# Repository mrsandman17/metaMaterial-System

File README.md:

# metaMaterial-System
The experiment system is used to measure transmission and reflection coefficents (S params) of a metamaterial.
The system includes a Keysight network Analyser to perform the measurement. A modifield CNC machine, controlled by an arduino unit, is used to move the metamaterial in order to perform measurements along an axis.
This repository details the programmtic aspect of the system. The getting started section will walk trough performing first measurements with the system. The About the System section will specify more details required to add more functinality or debug the system.

## Getting started
You can download the entire repository by clicking "Code" on the top right of the files window, and then "Download Zip".

### Measuring S parameters

#### Using the network analyser GUI
First connect your board for a S paramaters measurement. Like this:

We will test the system using the network analyser GUI by performing a measurement of S11 Parameter.
By using the program "Network Analyser" you can perform a simple measurement.
In order to perform the measurement:
1. Start the program "Network Analyser"
2. A window will pop out, select the instrument and press "Run"

3. Click "Power" -> "RF Power" -> "On"

4. You can change the number of sample points using "Sweep".

5. You can change the frequency range using "Freq"

5. Select "Trace" and press "Trace 1" to add a new trace.

6. Use "Meas" to select the S11 parameter

You now should be able to see your data. Note that clicking on "Preset" will also create a measurement of S11 parameter.
S21 parameter can be added by adding "Trace 2" in "Trace", and then selecting S21 in "Meas".

#### Measuring S parameters using the example script
After we verfied our data is good, we can automate the measurement process. A working code example is available in this repo.
The script  "measure_Sparams.m" is used to take a measurement of S11 and S21 parameters at a specified frequency range.
The script will connect to keysight network analyser, sample the data and plot S21 and S11 params. 
The frequency range can be changed with "START_FREQ" or "END_FREQ" constants.
The script does not set the number of sample points, this should be done through the GUI, as specified before, make sure to set "POINTS_NUM" constant to the same value.  

### Measuring X field
We can now measure the transmission field over an axis. For this purpose we will control an Arduino unit, the unit will control a motor which is  moving the surface the board is on.  In this measurement,  One cable is connected to the board and another functions as a sensor that scans the board. 

Connect the measure field system hardware (**Not detailed here**)

We will command the Arduino using GRBL. The current Arduino should already have the grbl library code uploaded, but if it doesn't, it can be found in this repo, under "grblUpload". It should be uploaded to the arudino unit (**Only on first use**).
This can be done via arduino gui, click on the file "grblUpload" and then upload it:

When the arduino is ready, we can communicate with it by sending GCode commands. We will first communicate with it using a java based program called "Universal-Gcode-Sender". Using the program, connect to the arduino port (Usually “COM3”) and try to send a command that will move the the motor a bit to one side (For instance, send X+ with a Step size of 0.1). 

Note that The GCODE commands you send are printed, We will later send those commands via Matlab. 

When you are done, make sure to disconnect from the arduino by clicking on close, this will free up the COM port.
**When first debugging the system, make sure to move the motor in small steps.**

#### Using the example script to measure X field.
Under "measureField" in this repository you can find the script "measure_x_field.m". This script will connect to keysight network analyser and the arduino unit and perform a full measurement of the board over the X axis. 

The script uses two utility functions: 

  - "doMeasurment.m" - Performs a measurement on an instrument object and returns its results.

  - "doGCodeCommand.m" - Executes a gCode command on an arduino object.

  **Before running measureField, Make sure to move the sensor to where the board starts! This can be done manually or through the program Universal-Gcode-Sender. This only needs to be done once, as the sensor will return to this location after the measurement is complete.**
  
## About the system

### The IVI driver
#### Using Keysight Command Expert
The computer communicates with the network analyzer using SCPI protocol. The keysight driver wraps this protocol with an easier to use driver interface called IVI. In this tutorial we will demonstrate how to communicate with the device using IVI-C. IVI-C interface can be viewed with the program “Keysight Command Expert”. 
Using this program we can run and simulate the commands we need on the device, and export them as Matlab commands.
To connect to the network analyser with the command expert:

1. Start the Program "Keysight command expert".

2. Create a new instrument driver object by clicking on "new Instrument" (**Only on first use, the instrument will be saved**)

3. Select "Connect to a real instrument"

4. Follow the wizard until this screen, select AgNA with the type "IVI-C"

5. Click Connect.

The device should appear green in "Active Instruments" the left side of the screen. We can look for more commands, view their documentation and export their code to Matlab. To add a command:
1. Select the command using the dropdown menu

2. Select it's parameters.

3. Add it to the command sequence: "Add Step" / "Add Step & Execute"

4. The command should appear at the buttom of the screen

4. Export the command by pressing "File" -> "Export Sequence"

#### General IVI command flow:
1. Init and reset the device (Removes all previous measurements). using the command:
```
initwithoptions
```
2. Configure pre-measurement data. for example, frequency range can be altered using:
```
channelstimulusrangeconfigurestartstop
```
3. Create a channel measurement. using the command:
```
channelmeasurementsadd
```
4. fetching the measurement data, using the command:
```
channelmeasurementfetchformatted
```
The return value of this command is the measurement data.

(screenshot of command with params)

After the commands were added you can export the commands using the export option, The result will be a template Matlab code. Note that The return value of the fetch command should be saved, as this is measurement data. In addition, changing to meaningfull variable and parameter names is advised. 
Be sure to disconnect from the device after usage, using these commands in matlab:
```
disconnect(instrument); 
delete(instrument);
```

Note that alternatively, Matlab can be used to get the commands, instead of the Command Expert. This can be achieved via accessing ”Matlab Instrument Driver” (can be accessed by typing “tmtool” into the command window).

### Working with the Arduino unit

The commands for working with arduino in matlab:
- Create a new serial connection:
```
arduino = serial('COM3', 'BaudRate', 115200);
set(arduino, 'TimeOut', 10);
```
- GCode commands can now be sent to the arduino:
```
fprintf(arduino, gCodeCommand);
confirm = fgetl(arduino);
```
- Make sure to close the connection to arduino, This can be achieved with:
```
out = instrfind;
flcose(out);
```

### FAQ
##
**Q:** How can we change the number of sample points in Keysight? 

**A:** This can be changed through the keysight GUI ("Network Analyser").
(screenshot) 
Note that this is possible because changes made through the GUI "Network Analyser" will also affect the script.
##
**Q:** The script can't connect to arduino because it is being used. 

**A:** Make sure you closed any open connections to the arduino. through the script or through the GUI "Universal-Gcode-Sender"
```
out = instrfind;
flcose(out);
```
##
**Q:** What is the flow of using IVI commands in matlab?

**A:** The flow consists of several steps:
- We create an instrument object and connect to it thus connecting to the network analyser driver.
```
makemid('AgNA','AgNA.mdd')
instrument = icdevice('AgNA.mdd', 'PXI10::0-0.0::INSTR');
connect(instrument);
```
- We reset and init the device.
```
invoke(instrument,'initwithoptions','PXI10::0-0.0::INSTR',false,true,"")
```
- We can access a sub object of the intrument by using the get command, then we can invoke commands on that sub object. For example in order to init the frequency range of the measurement:
```
ChannelStimulusRange = get(instrument, 'Channelstimulusrange');
invoke(ChannelStimulusRange, 'channelstimulusrangeconfigurestartstop', string(CHANNEL_NUM), START_FREQ, END_FREQ);
```
The last invoke command will execute the ivi command 'channelstimulusrangeconfigurestartstop' on he sub-object "ChannelStimulusRange" with the parameters: string(CHANNEL_NUM), START_FREQ, END_FREQ.
##
**Q:** Which IVI commands will return values?

**A:** A get command will return the sub-object. But some invoke commands will also return values.
For example, lets look at the fetch formatted command:
```
[s21,s21Size] = invoke(channelMeasurment, 'channelmeasurementfetchformatted', repCapidentifier, BUFFER_SIZE, s21);
```
This command will call 'channelmeasurementfetchformatted' on channelMeasurment sub-object of the instrument with the parameters:

- repCapidentifier - the measrument identifirer string. In the format: "Channel{CHANNEL_NUM}:Measurment{MEASURMENT_NUM}"

- BUFFER_SIZE -The size of the buffer (make sure it is big enough)

- s21 - The initial array of the results

The command will return the sampled s21 array and its size.(The size is determined from the number of sample points in keysight)

##
**Q:** How can we look for more IVI-commands?

**A:** You can look for more commands at "Keysight command expert" program or through matlab instrument driver: "tmtool"-> Look for the instrument and connect to it, documentation of the avaible commands can be found in this window. Make sure to send the correct parameter types (string, int). The command expert method might be easier to use.
##

##
**Q:** We replaced the System motor, what are the changes needed from the programmatic side?

**A:** The current script assumes that the Gcode command +X 0.1 will move it by one millimeter. If the motor is changed you will need to remeasure it. The easiest way might be to send a move command with "Uiniversal-GCode-Sender" GUI and measure how the board moved with a  ruler. If the value has indeed changed, you can edit the values in the script with the "G_MOVE_X_RIGHT, "G_MOVE_X_LEFT" constants.
```
G_MOVE_X_RIGHT = "G21G91G1X0.1F25";
G_MOVE_X_LEFT = "G21G91G1X-0.1F25";
```
Change the value "0.1" in the command for whatever value that corresponds to 1mm.
##

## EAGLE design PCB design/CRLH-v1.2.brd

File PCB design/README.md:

# PCB Design 
The pcb was designed in Eagle and can be modified to create CRLH with diffrent parameters. 

## Tips
1. Cell blocks of the CRLH are SMD pads. Pads should be designed bearing in mind that the thickness (usally set to 35 um) and width should
  be set to give 50 Ohm impedance. 
2. Flood all the suface of the pcb with one common ground. connect all grounds, pads and connectors, to the same common ground.

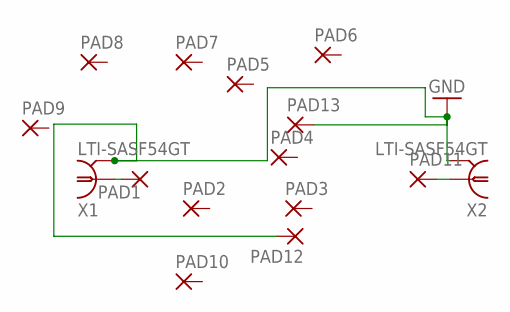
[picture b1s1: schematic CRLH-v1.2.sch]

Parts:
PAD1, PAD2, PAD3, PAD4, PAD5, PAD6, PAD7, PAD8, PAD9, PAD10, PAD11, PAD12, PAD13: SMD5; SMD2,54-5,08
X1, X2: LTI-SASF54GT

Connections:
GND: PAD12.1, PAD13.1, X1.2, X1.3 (2), X1.4 (2), X1.5 (2), X2.2, X2.3 (2), X2.4 (2), X2.5 (2)
unnamed: PAD1.1, X1.1
PAD11: PAD11.1, X2.1

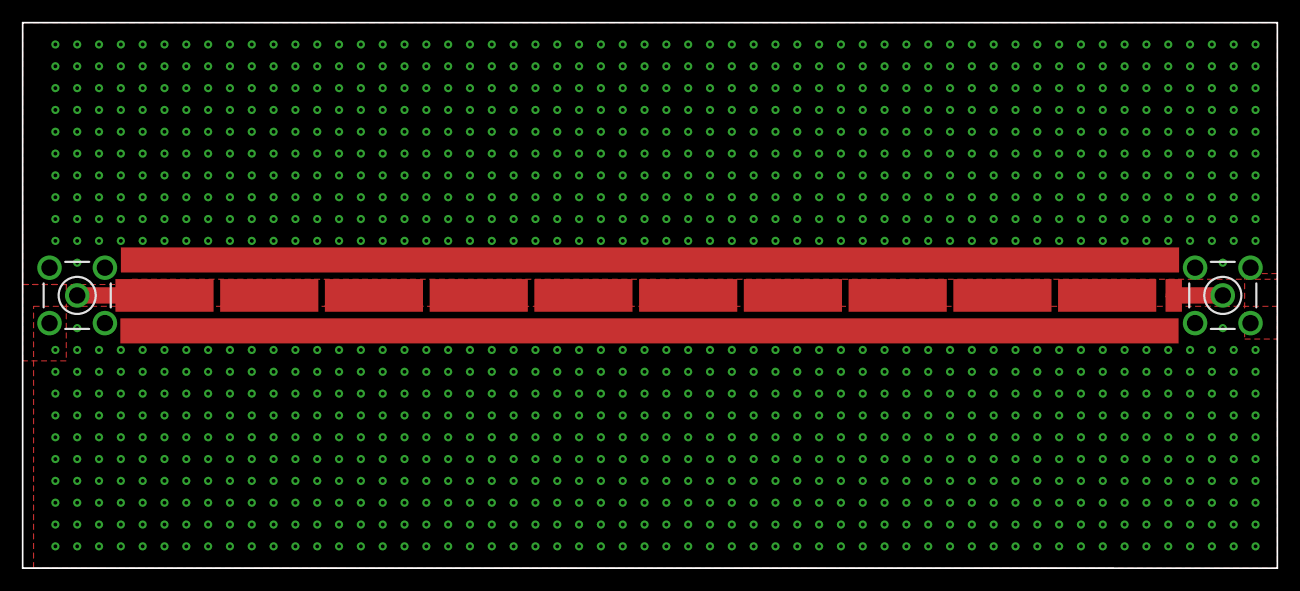
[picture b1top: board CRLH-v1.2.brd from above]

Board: 2 copper layers, 115.0 x 50.0 mm, 15 parts (0 on the bottom side), 3 nets.

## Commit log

2021-03-05 Add code and pics
